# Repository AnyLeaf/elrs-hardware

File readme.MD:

# AnyLeaf ELRS 2.4Ghz diversity Rx hardware

This repo contains published hardware information for the AnyLeaf ELRS receivers.
It contains schematics, KiCad schematic and PCB layout files, and production files
(Gerbers, drill files, bill of materials (BOM), and pick+place files). If you have any questions
or concerns, please post a Github issue here, or contact us at [anyleaf@anyleaf.org](mailto:anyleaf@anyleaf.org).

## This repo contains 2 designs:
- Single radio (SX1280), with ESP8285 MCU, and SkyWorks SE2431 LNA/PA/antenna mux.
- Dual radio (SX1280), with ESP32-PICO-V3 MCU, and SkyWorks RFX2401C LNA/PAs.

Images of the schematics are provided as PNG files in the main repo; this is the easiest
way to view the schematics.

To view details, including PCB layouts, open the schematic and/or PCB files in 
[KiCad](https://www.kicad.org/).

For info on specific parts chosen, including part numbers at Digikey and LCSC, open
the schematic files in KiCad, and examine part properties.

All parts are on the same side of the PCB. Resistors and capacitors are *0402* size.

## [ExpressLRS home page](https://www.expresslrs.org/3.0/)

## [ExpressLRS hardware repo](https://github.com/ExpressLRS/ExpressLRS-Hardware)

## [AnyLeaf single-radio 2.4Ghz receiver](https://www.anyleaf.org/elrs-rx)

## [AnyLeaf dual-radio 2.4Ghz receiver](https://www.anyleaf.org/elrs-rx-dualradio)

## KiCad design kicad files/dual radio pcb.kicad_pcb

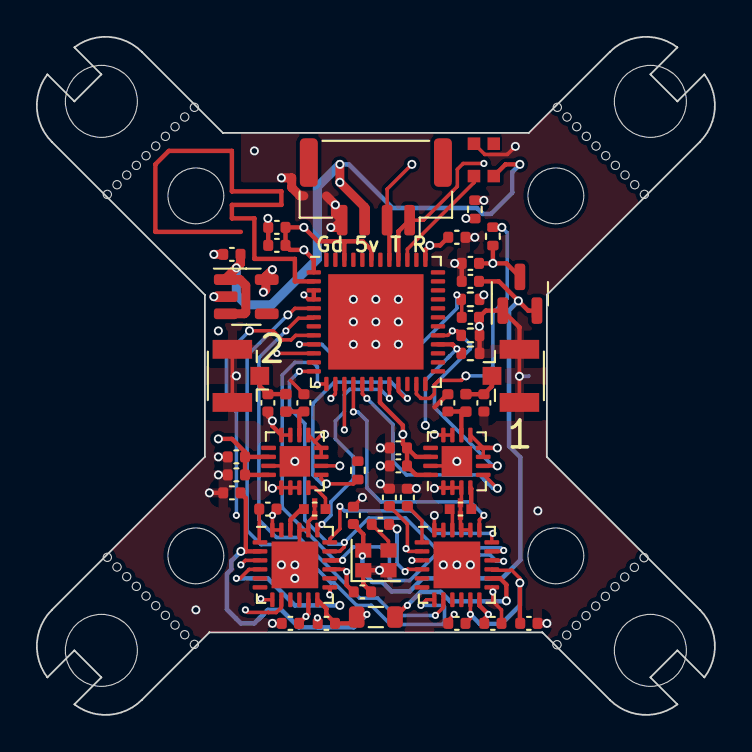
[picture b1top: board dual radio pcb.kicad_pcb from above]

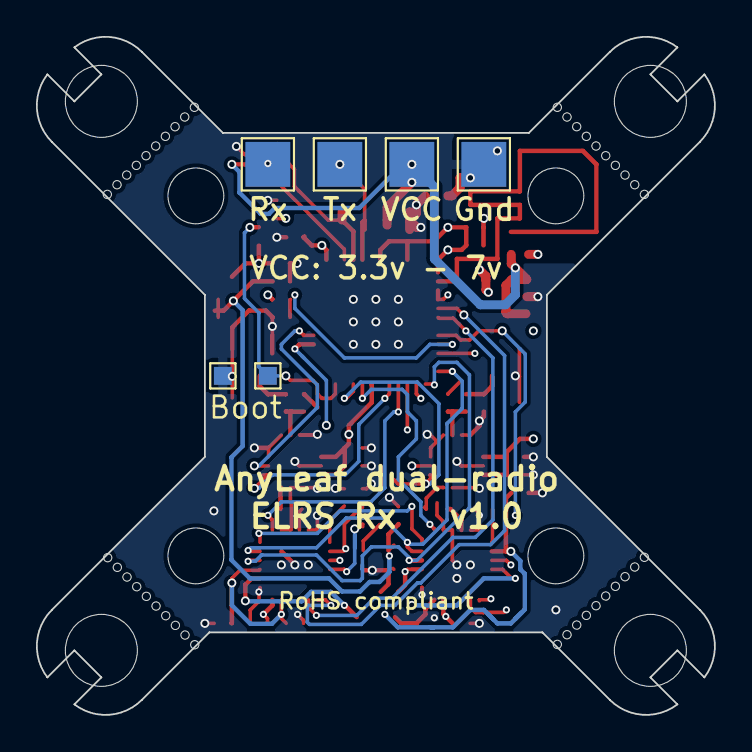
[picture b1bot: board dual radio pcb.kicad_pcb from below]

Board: 4 copper layers, 37.7 x 37.7 mm, 68 parts (6 on the bottom side), 37 nets.

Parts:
C1, C24, C25: 1u; C_0402_1005Metric
C2: 2.2u; C_0402_1005Metric
C3, C5, C11, C13: 10n; C_0402_1005Metric
C4, C12: 470n, 10V; C_0402_1005Metric
C6, C7, C8, C14, C15, C16, C18, C21: 100n; C_0402_1005Metric
C9: 10u; C_0402_1005Metric
C10: 1u 25v; C_0402_1005Metric
C17, C20: 10p; C_0402_1005Metric
C19, C22, C26, C27: 1.2p; C_0402_1005Metric
C23: 1n; C_0402_1005Metric
D1: WS2812B; LED-APA102-2020
H1, H2, H3, H4, H7, H8, H9, H10: MountingHole; MountingHole_3.2mm_M3
H5, H6, H11, H12: MountingHole_Pad; Mouse bites_7mm
J1, J8: Conn_Coaxial; U.FL_Hirose_U.FL-R-SMT-1_Vertical
J2, J9: Conn_01x01_Female; TestPoint_Pad_1.0x1.0mm
J3, J4, J5, J6: Conn_01x01_Female; TestPoint_Pad_2.5x2.5mm
J7: Conn_01x04_Male; JST_GH_SM04B-GHS-TB_1x04-1MP_P1.25mm_Horizontal
L1: 15u; L_0805_2012Metric
L2, L3: 3n; L_0402_1005Metric
R1, R2: 10k; R_0402_1005Metric
R3, R4, R7, R8: 100k; R_0402_1005Metric
U1: 3V3. 500mA; TSOT-23-5
U2, U3: SX1281; QFN-24-1EP_4x4mm_P0.5mm_EP2.6x2.6mm
U4, U13: RFX2401C; QFN-16-1EP_3x3mm_P0.5mm_EP1.7x1.7mm
U7: ESP32-PICO-V3; QFN-48-1EP_7x7mm_P0.5mm_EP5.3x5.3mm
U9, U10: 2450FM07D0034T; 2450FM07D0034
U11: AP2138N-2.8TRG1; SOT-23
Y3: 52Mhz TCXO; Crystal_SMD_2016-4Pin_2.0x1.6mm

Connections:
+2V8: C16.1, C25.2, U11.2 (VO), Y3.4
+3V3: C2.2, C6.2, C7.2, C8.2, C9.2, C14.2, C15.2, C17.2, C18.1, C20.2, C21.1, C24.2, R1.1, R2.2, U1.5 (VOUT), U2.11 (VBAT_IO), U2.15 (VBAT), U3.11 (VBAT_IO), U3.15 (VBAT), U4.14 (VDD), U4.16 (VDD), U7.1 (VDDA), U7.3 (VDDA3P3), U7.4 (VDDA3P3), U7.19 (VDD3P3_RTC), U7.37 (VDD3P3_CPU), U7.43 (VDDA), U7.46 (VDDA), U11.3 (VI), U13.14 (VDD), U13.16 (VDD)
/ANT1: C19.1, L2.1, U13.10 (ANT)
/ANT2: C22.1, L3.1, U4.10 (ANT)
/BOOT: J2.1, R1.2, U7.23 (IO0)
/BUSY: U2.7 (BUSY), U7.5 (SENSOR_VP)
/BUSY_2: U3.7 (BUSY), U7.8 (SENSOR_VN)
/CS: U2.19 (NSS_CTS), U7.16 (IO27)
/CS_2: U3.19 (NSS_CTS), U7.20 (IO13)
/DIO: U2.8 (DIO1), U7.6 (SENSOR_CAPP)
/DIO_2: U3.8 (DIO1), U7.10 (IO34)
/LED: D1.3 (DIN), U7.39 (IO22)
/MISO: U2.16 (MISO_TX), U3.16 (MISO_TX), U7.13 (IO33)
/MOSI: U2.17 (MOSI_RX), U3.17 (MOSI_RX), U7.12 (IO32)
/PWR_IN: C1.2, D1.4 (VDD), J4.1, J7.3, U1.1 (VIN), U1.3 (~SHDN)
/PWR_RXEN: R7.2, U7.29 (SD3/IO10), U13.6 (RXEN)
/PWR_RXEN2: R3.2, U4.6 (RXEN), U7.28 (SD2/IO9)
/PWR_TXEN: R8.1, U7.17 (IO14), U13.5 (TXEN)
/PWR_TXEN2: R4.1, U4.5 (TXEN), U7.21 (IO15)
/RADIO_OSC: C23.2, U2.4 (XTA), U3.4 (XTA)
/RF_OUT1: U9.3, U13.4 (TXRX)
/RF_OUT2: U4.4 (TXRX), U10.3
/RST: U2.3 (NRESET), U3.3 (NRESET), U7.15 (IO26)
/SCK: U2.18 (SCK_RTSN), U3.18 (SCK_RTSN), U7.14 (IO25)
/UART_RX: J6.1, J7.1, U7.40 (U0RXD/IO3)
/UART_TX: J5.1, J7.2, U7.41 (U0TXD/IO1)
/V_DCC: C4.1, C5.2, C12.1, C13.2, L1.1, U2.2 (VDD_IN), U2.12 (DCC_FB), U3.2 (VDD_IN), U3.12 (DCC_FB)
/V_DCC2: L1.2, U2.14 (DCC_SW)
GND: C1.1, C2.1, C3.1, C4.2, C5.1, C6.1, C7.1, C8.1, C9.1, C10.2, C11.1, C12.2, C13.1, C14.1, C15.1, C16.2, C17.1, C18.2, C19.2, C20.1, C21.2, C22.2, C24.1, C25.1, C26.2, C27.2, D1.2 (VSS), J1.2 (Ext), J3.1, J7.4, J8.2 (Ext), J9.1, R3.1, R4.2, R7.1, R8.2, U1.2 (GND), U2.13 (GND), U2.20 (GND), U2.21 (GND), U2.23 (GND), U2.24 (GND), U2.25 (EP_GND), U3.13 (GND), U3.20 (GND), U3.21 (GND), U3.23 (GND), U3.24 (GND), U3.25 (EP_GND), U4.1 (GND), U4.2 (GND), U4.3 (GND), U4.7 (GND), U4.8 (GND), U4.9 (GND), U4.11 (GND), U4.12 (GND), U4.15 (GND), U4.17 (GND), U7.49 (GND), U9.2, U9.4, U10.2, U10.4, U11.1 (GND), U13.1 (GND), U13.2 (GND), U13.3 (GND), U13.7 (GND), U13.8 (GND), U13.9 (GND), U13.11 (GND), U13.12 (GND), U13.15 (GND), U13.17 (GND), Y3.1, Y3.2
unnamed: C23.1, Y3.3
unnamed: C26.1, J1.1 (In), L2.2
unnamed: C27.1, J8.1 (In), L3.2
unnamed: U2.22 (RFIO), U9.1
unnamed: C3.2, U2.1 (VR_PA)
unnamed: U3.22 (RFIO), U10.1
unnamed: C11.2, U3.1 (VR_PA)
unnamed: C10.1, R2.1, U7.9 (EN)

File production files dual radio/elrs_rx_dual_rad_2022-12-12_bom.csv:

Comment,Designator,Footprint,LCSC
"1u","C1,C24,C25","Capacitor_SMD:C_0402_1005Metric","C52923"
"1u 25v","C10","Capacitor_SMD:C_0402_1005Metric","C52923"
"10p","C17,C20","Capacitor_SMD:C_0402_1005Metric","C32949"
"2.2u","C2","Capacitor_SMD:C_0402_1005Metric","C12530"
"1n","C23","Capacitor_SMD:C_0402_1005Metric","C1523"
"10n","C3,C5,C11,C13","Capacitor_SMD:C_0402_1005Metric","C15195"
"470n, 10V","C4,C12","Capacitor_SMD:C_0402_1005Metric","C47339"
"100n","C6,C7,C8,C14,C15,C16,C18,C21","Capacitor_SMD:C_0402_1005Metric","C1525"
"10u","C9","Capacitor_SMD:C_0402_1005Metric","C15525"
"WS2812B","D1","LED_SMD:LED-APA102-2020","C965555"
"Conn_Coaxial","J1,J8","Connector_Coaxial:U.FL_Hirose_U.FL-R-SMT-1_Vertical","C88374"
"Conn_01x01_Female","J3,J4,J5,J6","TestPoint:TestPoint_Pad_2.5x2.5mm",""
"Conn_01x04_Male","J7","Connector_JST:JST_GH_SM04B-GHS-TB_1x04-1MP_P1.25mm_Horizontal","C189895"
"15u","L1,L2","Inductor_SMD:L_0805_2012Metric","C486333"
"10k","R1,R2","Resistor_SMD:R_0402_1005Metric","C25744"
"100k","R3,R4,R7,R8","Resistor_SMD:R_0402_1005Metric","C25741"
"3V3. 500mA","U1","Package_TO_SOT_SMD:TSOT-23-5","C587158"
"AP2138N-2.8TRG1","U11","Package_TO_SOT_SMD:SOT-23","C176956"
"AT2401C","U12,U13","Package_DFN_QFN:QFN-16-1EP_3x3mm_P0.5mm_EP1.7x1.7mm","C783588"
"SX1281","U2,U3","Package_DFN_QFN:QFN-24-1EP_4x4mm_P0.5mm_EP2.6x2.6mm","C2151551"
"2450FM07D0034T","U4,U5,U9,U10","Anyleaf_Shared:2450FM07D0034",""
"ESP32-PICO-V3","U7","Package_DFN_QFN:QFN-48-1EP_7x7mm_P0.5mm_EP5.3x5.3mm","C967022"
"52Mhz TCXO","Y3","Crystal:Crystal_SMD_2016-4Pin_2.0x1.6mm",""

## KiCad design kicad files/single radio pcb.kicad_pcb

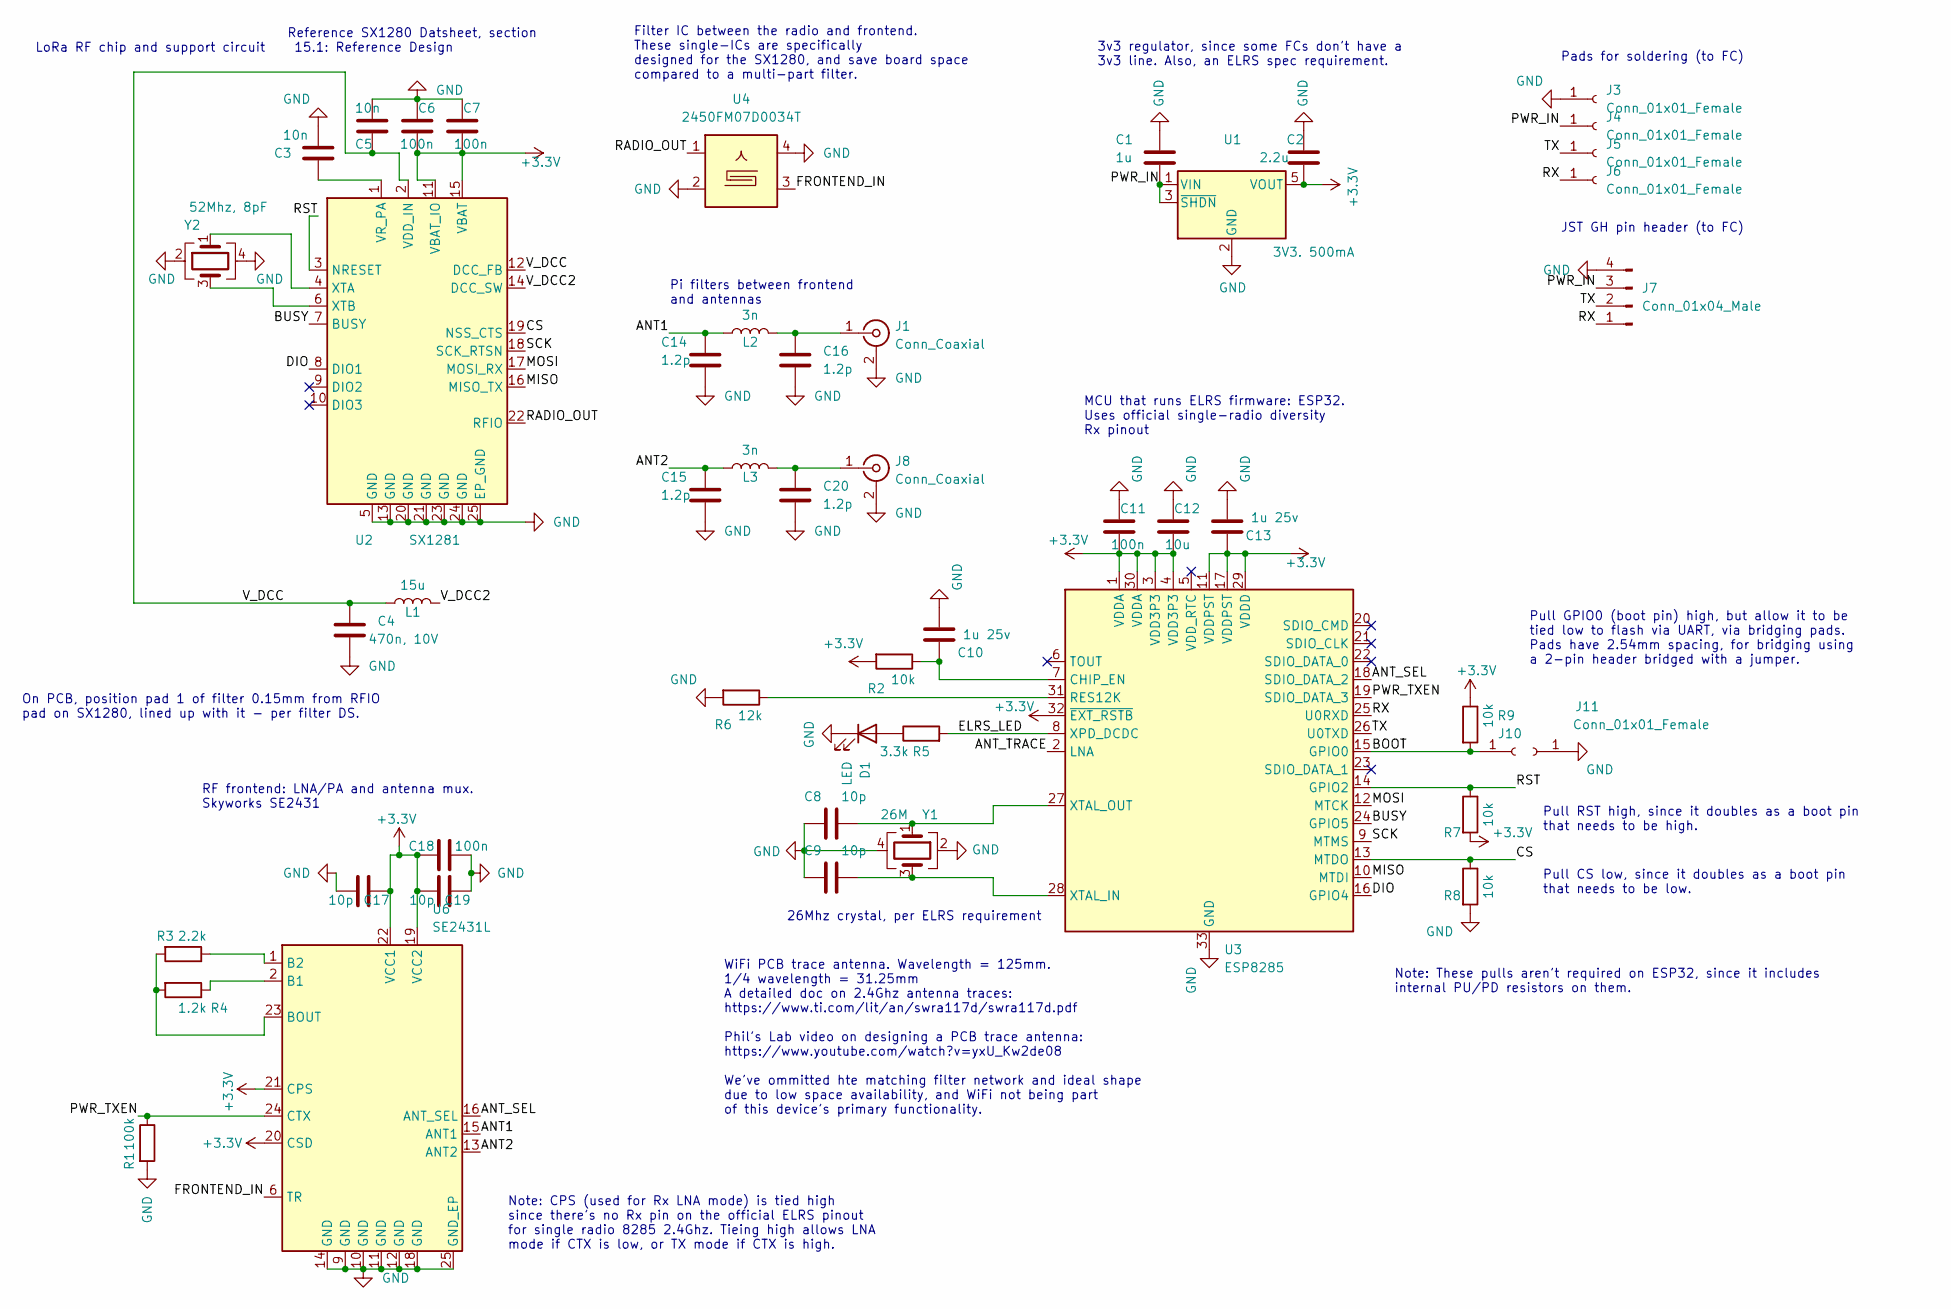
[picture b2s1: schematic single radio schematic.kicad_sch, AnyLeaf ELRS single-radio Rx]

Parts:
C1: 1u; C_0402_1005Metric; LCSC C52923
C2: 2.2u; C_0402_1005Metric; LCSC C12530
C3, C5: 10n; C_0402_1005Metric; LCSC C15195
C4: 470n, 10V; C_0402_1005Metric; LCSC C47339
C6, C7, C11, C18: 100n; C_0402_1005Metric; LCSC C1525
C8, C9, C17, C19: 10p; C_0402_1005Metric; LCSC C32949
C10, C13: 1u 25v; C_0402_1005Metric; LCSC C52923
C12: 10u; C_0402_1005Metric; LCSC C15525
C14, C15, C16, C20: 1.2p; C_0402_1005Metric; LCSC C327292
D1: LED; LED_0603_1608Metric; LCSC C2286
J1, J8: Conn_Coaxial; U.FL_Hirose_U.FL-R-SMT-1_Vertical; Part Hirose U.FL-R-SMT-1(80); LCSC C88374
J3, J4, J5, J6: Conn_01x01_Female; TestPoint_Pad_2.5x2.5mm
J7: Conn_01x04_Male; JST_GH_SM04B-GHS-TB_1x04-1MP_P1.25mm_Horizontal; LCSC C189895
J10, J11: Conn_01x01_Female; TestPoint_Pad_1.0x1.0mm
L1: 15u; L_0805_2012Metric; LCSC C486333
L2, L3: 3n; L_0402_1005Metric; LCSC C269824
R1: 100k; R_0402_1005Metric; LCSC C25741
R2, R7, R8, R9: 10k; R_0402_1005Metric; LCSC C25744
R3: 2.2k; R_0402_1005Metric; LCSC C25879
R4: 1.2k; R_0402_1005Metric; LCSC C25862
R5: 3.3k; R_0402_1005Metric; LCSC C25890
R6: 12k; R_0402_1005Metric; LCSC C25752
U1: 3V3. 500mA; TSOT-23-5; Part TPRT9013-33GB; LCSC C587158
U2: SX1281; QFN-24-1EP_4x4mm_P0.5mm_EP2.6x2.6mm; Digikey SX1281IMLTRTTR-ND
U3: ESP8285; QFN-32-1EP_5x5mm_P0.5mm_EP3.45x3.45mm; LCSC C967019
U4: 2450FM07D0034T; 2450FM07D0034; Mouser 609-2450FM07D0034T
U6: SE2431L; QFN-24-1EP_3x4mm_P0.4mm_EP1.65x2.65mm; Digikey 863-1347-2-ND
Y1: 26M; Crystal_SMD_2016-4Pin_2.0x1.6mm; LCSC C843259
Y2: 52Mhz, 8pF; Crystal_SMD_2016-4Pin_2.0x1.6mm; LCSC C781783

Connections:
+3V3: C2.2, C6.2, C7.2, C11.2, C12.2, C13.1, C17.2, C18.1, C19.1, R2.2, R7.2, R9.1, U1.5 (VOUT), U2.11 (VBAT_IO), U2.15 (VBAT), U3.1 (VDDA), U3.3 (VDD3P3), U3.4 (VDD3P3), U3.11 (VDDPST), U3.17 (VDDPST), U3.29 (VDDD), U3.30 (VDDA), U3.32 (~EXT_RSTB), U6.19 (VCC2), U6.20 (CSD), U6.21 (CPS), U6.22 (VCC1)
/ANT1: C14.1, L2.1, U6.15 (ANT1)
/ANT2: C15.1, L3.1, U6.13 (ANT2)
/ANT_SEL: U3.18 (SDIO_DATA_2), U6.16 (ANT_SEL)
/ANT_TRACE: U3.2 (LNA)
/BOOT: J10.1, R9.2, U3.15 (GPIO0)
/BUSY: U2.7 (BUSY), U3.24 (GPIO5)
/CS: R8.1, U2.19 (NSS_CTS), U3.13 (MTDO)
/DIO: U2.8 (DIO1), U3.16 (GPIO4)
/ELRS_LED: R5.2, U3.8 (XPD_DCDC)
/FRONTEND_IN: U4.3, U6.6 (TR)
/MISO: U2.16 (MISO_TX), U3.10 (MTDI)
/MOSI: U2.17 (MOSI_RX), U3.12 (MTCK)
/PWR_IN: C1.2, J4.1, J7.3, U1.1 (VIN), U1.3 (~SHDN)
/PWR_TXEN: R1.1, U3.19 (SDIO_DATA_3), U6.24 (CTX)
/RADIO_OUT: U2.22 (RFIO), U4.1
/RST: R7.1, U2.3 (NRESET), U3.14 (GPIO2)
/RX: J6.1, J7.1, U3.25 (U0RXD)
/SCK: U2.18 (SCK_RTSN), U3.9 (MTMS)
/TX: J5.1, J7.2, U3.26 (U0TXD)
/V_DCC: C4.1, C5.2, L1.1, U2.2 (VDD_IN), U2.12 (DCC_FB)
/V_DCC2: L1.2, U2.14 (DCC_SW)
GND: C1.1, C2.1, C3.1, C4.2, C5.1, C6.1, C7.1, C8.1, C9.1, C10.2, C11.1, C12.1, C13.2, C14.2, C15.2, C16.2, C17.1, C18.2, C19.2, C20.2, D1.1 (K), J1.2 (Ext), J3.1, J7.4, J8.2 (Ext), J11.1, R1.2, R6.2, R8.2, U1.2 (GND), U2.5 (GND), U2.13 (GND), U2.20 (GND), U2.21 (GND), U2.23 (GND), U2.24 (GND), U2.25 (EP_GND), U3.33 (GND), U4.2, U4.4, U4.5, U6.9 (GND), U6.10 (GND), U6.11 (GND), U6.12 (GND), U6.14 (GND), U6.18 (GND), U6.25 (GND_EP), Y1.2, Y1.4, Y2.2, Y2.4
unnamed: C3.2, U2.1 (VR_PA)
unnamed: C8.2, U3.27 (XTAL_OUT), Y1.1
unnamed: C9.2, U3.28 (XTAL_IN), Y1.3
unnamed: C10.1, R2.1, U3.7 (CHIP_EN)
unnamed: C16.1, J1.1 (In), L2.2
unnamed: C20.1, J8.1 (In), L3.2
unnamed: D1.2 (A), R5.1
unnamed: R3.1, U6.1 (B2)
unnamed: R3.2, R4.2, U6.23 (BOUT)
unnamed: R4.1, U6.2 (B1)
unnamed: R6.1, U3.31 (RES12K)
unnamed: U2.4 (XTA), Y2.1
unnamed: U2.6 (XTB), Y2.3

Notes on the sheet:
26Mhz crystal, per ELRS requirement
MCU that runs ELRS firmware: ESP32. Uses official single-radio diversity Rx pinout
JST GH pin header (to FC)
Note: These pulls aren't required on ESP32, since it includes internal PU/PD resistors on them.
Pi filters between frontend and antennas
Pads for soldering (to FC)
Note: CPS (used for Rx LNA mode) is tied high since there's no Rx pin on the official ELRS pinout for single radio 8285 2.4Ghz. Tieing high allows LNA mode if CTX is low, or TX mode if CTX is high.
3v3 regulator, since some FCs don't have a 3v3 line. Also, an ELRS spec requirement.
WiFi PCB trace antenna. Wavelength = 125mm. 1/4 wavelength = 31.25mm A detailed doc on 2.4Ghz antenna traces: https://www.ti.com/lit/an/swra117d/swra117d.pdf Phil's Lab video on designing a PCB trace antenna: https://www.youtube.com/watch?v=yxU_Kw2de08 We've ommitted hte matching filter network and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
Pull CS low, since it doubles as a boot pin that needs to be low.
Reference SX1280 Datsheet, section 15.1: Reference Design
RF frontend: LNA/PA and antenna mux. Skyworks SE2431
Pull GPIO0 (boot pin) high, but allow it to be tied low to flash via UART, via bridging pads. Pads have 2.54mm spacing, for bridging using a 2-pin header bridged with a jumper.
On PCB, position pad 1 of filter 0.15mm from RFIO pad on SX1280, lined up with it - per filter DS.
Pull RST high, since it doubles as a boot pin that needs to be high.
LoRa RF chip and support circuit
Filter IC between the radio and frontend. These single-ICs are specifically designed for the SX1280, and save board space compared to a multi-part filter.

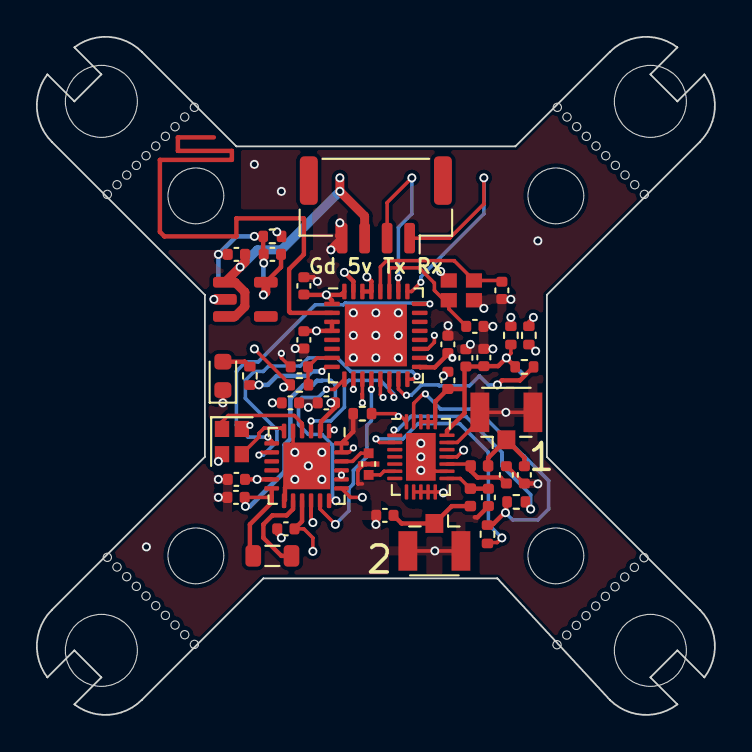
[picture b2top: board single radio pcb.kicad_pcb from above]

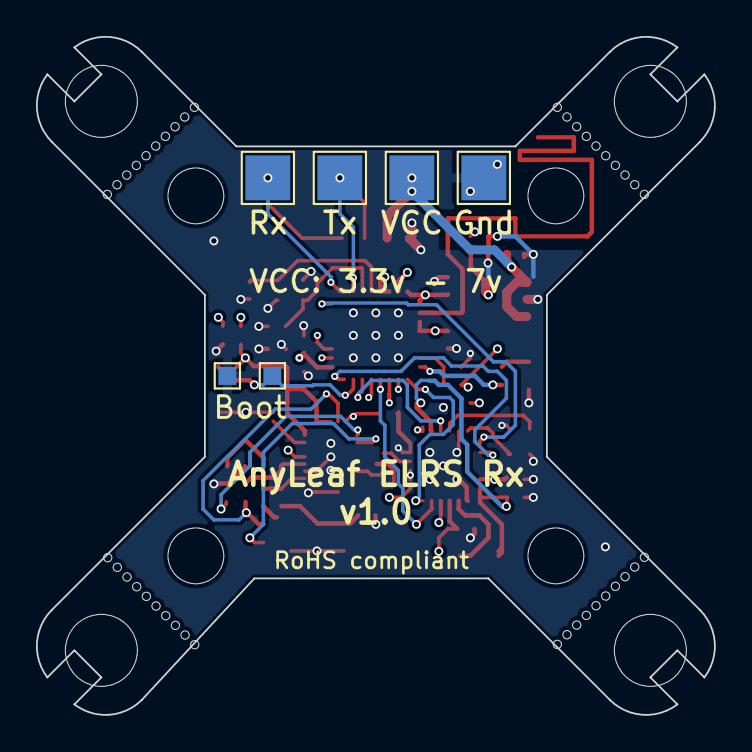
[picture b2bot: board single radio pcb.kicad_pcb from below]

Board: 4 copper layers, 37.7 x 37.7 mm, 61 parts (6 on the bottom side), 35 nets.

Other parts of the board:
H1, H2, H3, H4, H7, H8, H9, H10: MountingHole; MountingHole_3.2mm_M3
H5, H6, H11, H12: MountingHole_Pad; Mouse bites_7mm

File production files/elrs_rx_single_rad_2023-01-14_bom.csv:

Comment,Designator,Footprint,LCSC
"1u","C1","Capacitor_SMD:C_0402_1005Metric","C52923"
"1u 25v","C10,C13","Capacitor_SMD:C_0402_1005Metric","C52923"
"10u","C12","Capacitor_SMD:C_0402_1005Metric","C15525"
"2.2u","C2","Capacitor_SMD:C_0402_1005Metric","C12530"
"10n","C3,C5","Capacitor_SMD:C_0402_1005Metric","C15195"
"470n, 10V","C4","Capacitor_SMD:C_0402_1005Metric","C47339"
"100n","C6,C7,C11,C18","Capacitor_SMD:C_0402_1005Metric","C1525"
"10p","C8,C9,C17,C19","Capacitor_SMD:C_0402_1005Metric","C32949"
"LED","D1","LED_SMD:LED_0603_1608Metric","C2286"
"Conn_Coaxial","J1,J8","Connector_Coaxial:U.FL_Hirose_U.FL-R-SMT-1_Vertical","C88374"
"Conn_01x01_Female","J11","TestPoint:TestPoint_Pad_1.0x1.0mm",""
"Conn_01x01_Female","J3,J4,J5,J6","TestPoint:TestPoint_Pad_2.5x2.5mm",""
"Conn_01x04_Male","J7","Connector_JST:JST_GH_SM04B-GHS-TB_1x04-1MP_P1.25mm_Horizontal","C189895"
"15u","L1","Inductor_SMD:L_0805_2012Metric","C486333"
"100k","R1","Resistor_SMD:R_0402_1005Metric","C25741"
"10k","R2,R7,R8,R9","Resistor_SMD:R_0402_1005Metric","C25744"
"2.2k","R3","Resistor_SMD:R_0402_1005Metric","C25879"
"1.2k","R4","Resistor_SMD:R_0402_1005Metric","C25862"
"3.3k","R5","Resistor_SMD:R_0402_1005Metric","C25890"
"12k","R6","Resistor_SMD:R_0402_1005Metric","C25752"
"3V3. 500mA","U1","Package_TO_SOT_SMD:TSOT-23-5","C587158"
"SX1281","U2","Package_DFN_QFN:QFN-24-1EP_4x4mm_P0.5mm_EP2.6x2.6mm","C2151551"
"ESP8285","U3","Package_DFN_QFN:QFN-32-1EP_5x5mm_P0.5mm_EP3.45x3.45mm","C967019"
"2450FM07D0034T","U4,U5","Anyleaf_Shared:2450FM07D0034",""
"SE2431L","U6","Package_DFN_QFN:QFN-24-1EP_3x4mm_P0.4mm_EP1.65x2.65mm","C2649471"
"26M","Y1","Crystal:Crystal_SMD_2016-4Pin_2.0x1.6mm","C843259"
"52Mhz, 12pF","Y2","Crystal:Crystal_SMD_2016-4Pin_2.0x1.6mm",""

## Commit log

2023-01-14 Adjusted readme formatting
2023-01-14 Readme update
2023-01-14 folder rename
2023-01-14 clarify which designs are included
2023-01-14 Troubleshooting disapeared gerbers
2023-01-14 More details in readme
2023-01-14 Updated dual radio to eliminate second rad's inductor
2023-02-11 Updates including dif filter by antenna, better WiFi PCB antenna, and single inductor
2023-03-12 Updated dual rad to use RFX2401C frontends
2023-03-12 updated readme with more frontend info
